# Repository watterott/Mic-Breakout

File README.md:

# Mic-Breakout
Breakout with pre-amplified condenser microphone.

* Condenser Microphone or MEMS Microphone (v1.3+)
* [Maxim MAX4465](https://www.maximintegrated.com/en/products/analog/audio/MAX4465.html) Preamplifier
* Open-Source and released under the [Creative Commons Attribution Share-Alike License](https://creativecommons.org/licenses/by-sa/4.0/).
* **[Documentation on learn.watterott.com](https://learn.watterott.com)**

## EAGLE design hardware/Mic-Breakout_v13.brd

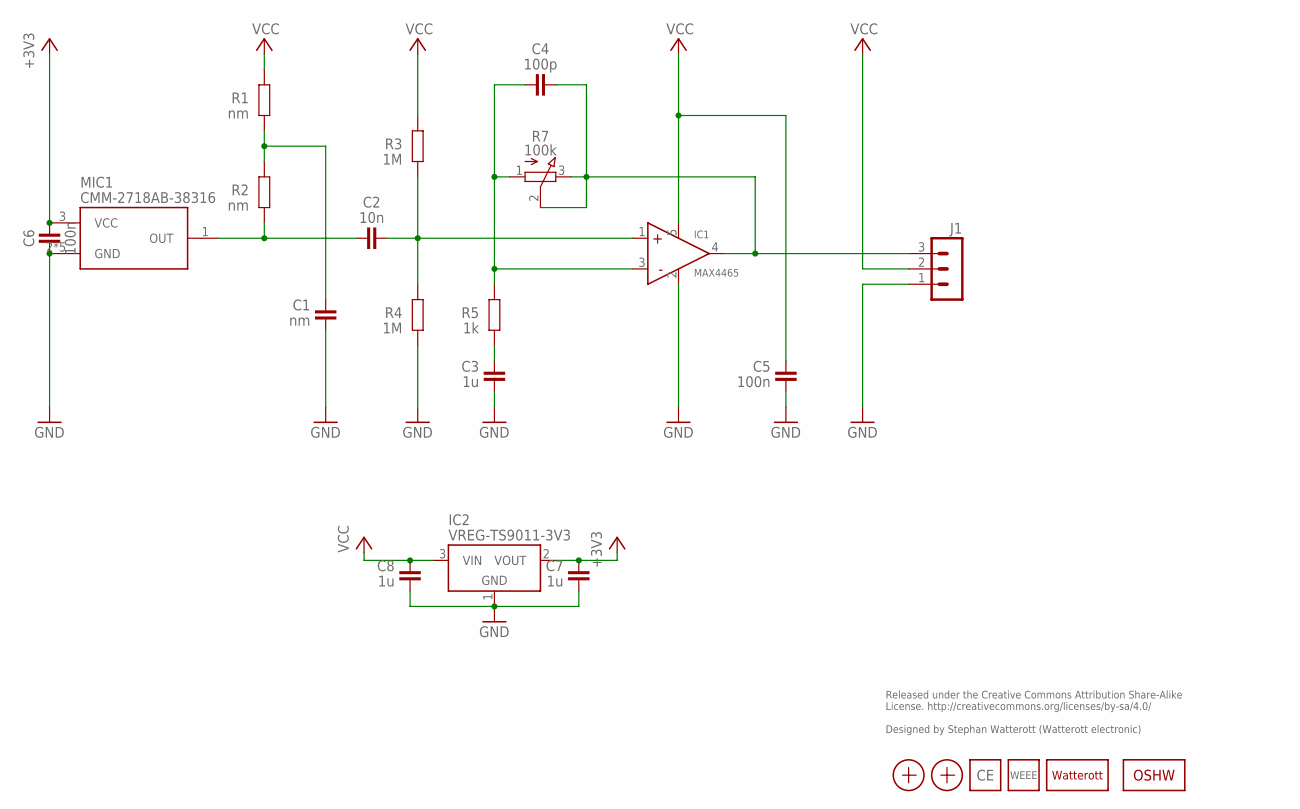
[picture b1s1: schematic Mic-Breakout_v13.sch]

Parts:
C1: nm; C0402
C2: 10n; C0402
C3, C7, C8: 1u; C0402
C4: 100p; C0402
C5, C6: 100n; C0402
IC1: MAX4465; SOT353
IC2: VREG-TS9011-3V3; SOT23
J1: MA03-1
LOGO1: LOGO-S_PLACE_M; SPARK_TPLACE_M
LOGO2: OSHW_LOGOX0100; OSHW_6X100
LOGO3: LOGO_WEEE-4; WEEE_4MM
LOGO4: LOGO_CE-2; CE_2MM
MIC1: CMM-2718AB-38316
R1, R2: nm; C0402
R3, R4: 1M; C0402
R5: 1k; C0402
R7: 100k; POT_EVM3Y
X1, X2: PASSER-04; PASSER_04MM

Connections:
+3V3: C6.2, C7.2, IC2.2 (VOUT), MIC1.3 (VCC)
GND: C1.1, C3.1, C5.1, C6.1, C7.1, C8.1, IC1.2 (GND), IC2.1 (GND), J1.1, MIC1.2 (GND), MIC1.4 (GND), MIC1.5 (GND), MIC1.6 (GND), MIC1.7 (GND), R4.1
unnamed: C1.2, R1.1, R2.2
unnamed: C2.2, IC1.1 (+), R3.1, R4.2
unnamed: C4.1, IC1.4 (OUT), J1.3, R7.2 (S), R7.3 (E)
unnamed: C2.1, MIC1.1 (OUT), R2.1
unnamed: C4.2, IC1.3 (-), R5.2, R7.1 (A)
unnamed: C3.2, R5.1
VCC: C5.2, C8.2, IC1.5 (VCC), IC2.3 (VIN), J1.2, R1.2, R3.2

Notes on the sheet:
Released under the Creative Commons Attribution Share-Alike License. http://creativecommons.org/licenses/by-sa/4.0/ Designed by Stephan Watterott (Watterott electronic)

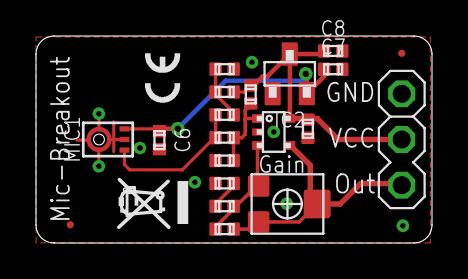
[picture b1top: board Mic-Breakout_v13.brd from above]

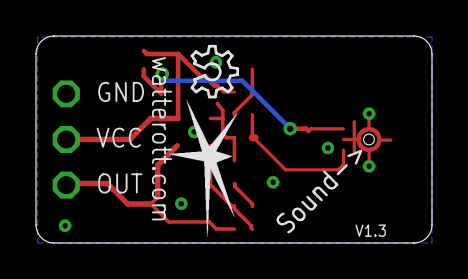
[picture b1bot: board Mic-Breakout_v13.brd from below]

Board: 2 copper layers, 22.0 x 11.5 mm, 24 parts (2 on the bottom side), 9 nets.

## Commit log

2020-09-27 added V1.3
